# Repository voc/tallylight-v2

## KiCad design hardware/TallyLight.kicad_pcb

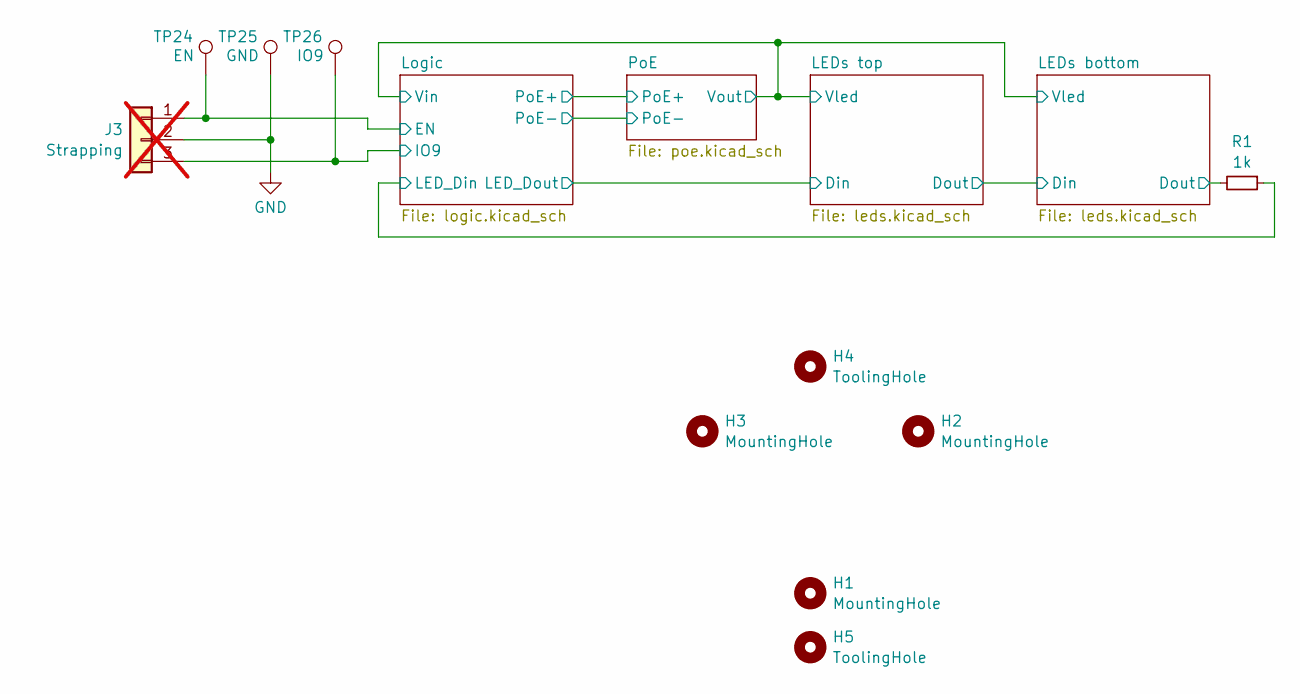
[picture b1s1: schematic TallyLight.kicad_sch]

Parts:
H1, H2, H3: MountingHole; MountingHole_3.2mm_M3
H4, H5: ToolingHole; ToolingHole_JLCSMT
J3: Strapping; PinHeader_1x03_P2.54mm_Vertical; not fitted
R1: 1k; R_0402_1005Metric; LCSC C11702
TP24: EN; TestPoint_Pad_D2.0mm_no_outline
TP25: GND; TestPoint_Pad_D2.0mm
TP26: IO9; TestPoint_Pad_D2.0mm_no_outline

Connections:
/LEDs bottom/Dout: R1.2; also elsewhere on the board
/Logic/EN: J3.1, TP24.1; also elsewhere on the board
/Logic/IO9: J3.3, TP26.1; also elsewhere on the board
/Logic/LED_Din: R1.1; also elsewhere on the board
GND: J3.2, TP25.1; also elsewhere on the board

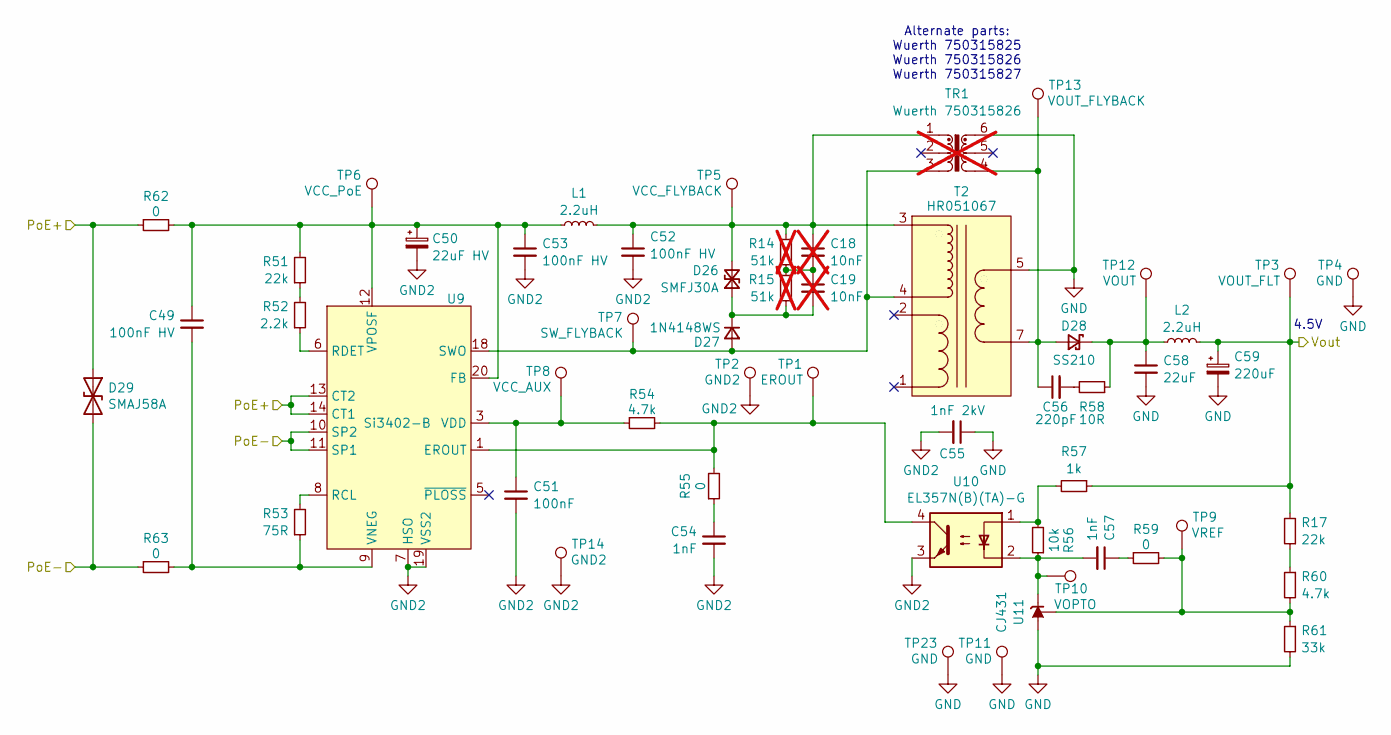
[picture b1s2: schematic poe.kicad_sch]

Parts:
C18, C19: 10nF; C_0402_1005Metric; LCSC C15195; not fitted
C49, C52, C53: 100nF HV; C_0805_2012Metric; LCSC C28233
C50: 22uF HV; CP_Elec_6.3x7.7; LCSC C344075
C51: 100nF; C_0402_1005Metric; LCSC C1525
C54, C57: 1nF; C_0402_1005Metric; LCSC C1523
C55: 1nF 2kV; C_1206_3216Metric; LCSC C9196
C56: 220pF; C_0402_1005Metric; LCSC C1530
C58: 22uF; C_0805_2012Metric; LCSC C45783
C59: 220uF; CP_Elec_6.3x7.7; LCSC C5243829
D26: SMFJ30A; D_SOD-123F; LCSC C151895
D27: 1N4148WS; D_SOD-323; LCSC C2128
D28: SS210; D_SMA; LCSC C14996
D29: SMAJ58A; D_SMA; LCSC C2980408
L1, L2: 2.2uH; L_1008_2520Metric; LCSC C964122
R14, R15: 51k; R_0402_1005Metric; LCSC C25794; not fitted
R17, R51: 22k; R_0402_1005Metric; LCSC C25768
R52: 2.2k; R_0402_1005Metric; LCSC C25879
R53: 75R; R_0603_1608Metric; LCSC C23242
R54, R60: 4.7k; R_0402_1005Metric; LCSC C25900
R55, R59, R62, R63: 0; R_0402_1005Metric; LCSC C17168
R56: 10k; R_0402_1005Metric; LCSC C25744
R57: 1k; R_0402_1005Metric; LCSC C11702
R58: 10R; R_0402_1005Metric; LCSC C25077
R61: 33k; R_0402_1005Metric; LCSC C25779
T2: HR051067; LCSC C93830
TP1: EROUT; TestPoint_Pad_D2.0mm_no_outline
TP2, TP14: GND2; TestPoint_Pad_D2.0mm_trianglular_outline
TP3: VOUT_FLT; TestPoint_Pad_D2.0mm_no_outline
TP4, TP11, TP23: GND; TestPoint_Pad_D2.0mm
TP5: VCC_FLYBACK; TestPoint_Pad_D2.0mm_no_outline
TP6: VCC_PoE; TestPoint_Pad_D2.0mm_no_outline
TP7: SW_FLYBACK; TestPoint_Pad_D2.0mm_no_outline
TP8: VCC_AUX; TestPoint_Pad_D2.0mm_no_outline
TP9: VREF; TestPoint_Pad_D2.0mm_no_outline
TP10: VOPTO; TestPoint_Pad_D2.0mm_no_outline
TP12: VOUT; TestPoint_Pad_D2.0mm_no_outline
TP13: VOUT_FLYBACK; TestPoint_Pad_D2.0mm_no_outline
TR1: Wuerth 750315826; Transformer_Wuerth_750315371; not fitted
U9: Si3402-B; QFN-20-1EP_5x5mm_P0.8mm_EP2.7x2.7mm; LCSC C510771
U10: EL357N(B)(TA)-G; PC817CS_SMD; LCSC C20612591
U11: CJ431; SOT-23; LCSC C3113

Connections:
/LEDs bottom/Vled: C59.1, L2.2, R17.2, R57.1, TP3.1; also elsewhere on the board
/Logic/PoE+: D29.1 (A1), R62.1, U9.13 (CT2), U9.14 (CT1); also elsewhere on the board
/Logic/PoE-: D29.2 (A2), R63.1, U9.10 (SP2), U9.11 (SP1); also elsewhere on the board
GND: C55.1, C58.2, C59.2, R61.2, T2.5, T2.6, TP4.1, TP11.1, TP23.1, TR1.6, U11.3 (A); also elsewhere on the board
GND2: C50.2, C51.2, C52.2, C53.2, C54.2, C55.2, TP2.1, TP14.1, U9.7 (HSO), U9.19 (VSS2), U10.3
unnamed: C18.2, C19.1, R14.1, R15.2
unnamed: C49.2, R53.1, R63.2, U9.9 (VNEG), U9.21 (VNEG)
unnamed: C54.1, R55.1
unnamed: C56.2, R58.2
unnamed: C57.1, R59.1
unnamed: C19.2, D26.1 (A1), D27.1 (K), R15.1
unnamed: C18.1, C52.1, D26.2 (A2), L1.2, R14.2, T2.3, TP5.1, TR1.1
unnamed: D27.2 (A), T2.4, TP7.1, TR1.3, U9.18 (SWO)
unnamed: C56.1, D28.2 (A), T2.7, T2.8, TP13.1, TR1.4
unnamed: C58.1, D28.1 (K), L2.1, R58.1, TP12.1
unnamed: R17.1, R60.1
unnamed: R51.1, R52.2
unnamed: R56.2, R57.2, U10.1
unnamed: R54.2, R55.2, TP1.1, U9.1 (EROUT), U10.4
unnamed: C49.1, C50.1, C53.1, L1.1, R51.2, R62.2, TP6.1, U9.12 (VPOSF), U9.20 (FB)
unnamed: R53.2, U9.8 (RCL)
unnamed: R52.1, U9.6 (RDET)
unnamed: C51.1, R54.1, TP8.1, U9.3 (VDD)
unnamed: C57.2, R56.1, TP10.1, U10.2, U11.2 (K)
unnamed: R59.2, R60.2, R61.1, TP9.1, U11.1 (REF)

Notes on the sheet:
4.5V
Alternate parts: Wuerth 750315825 Wuerth 750315826 Wuerth 750315827

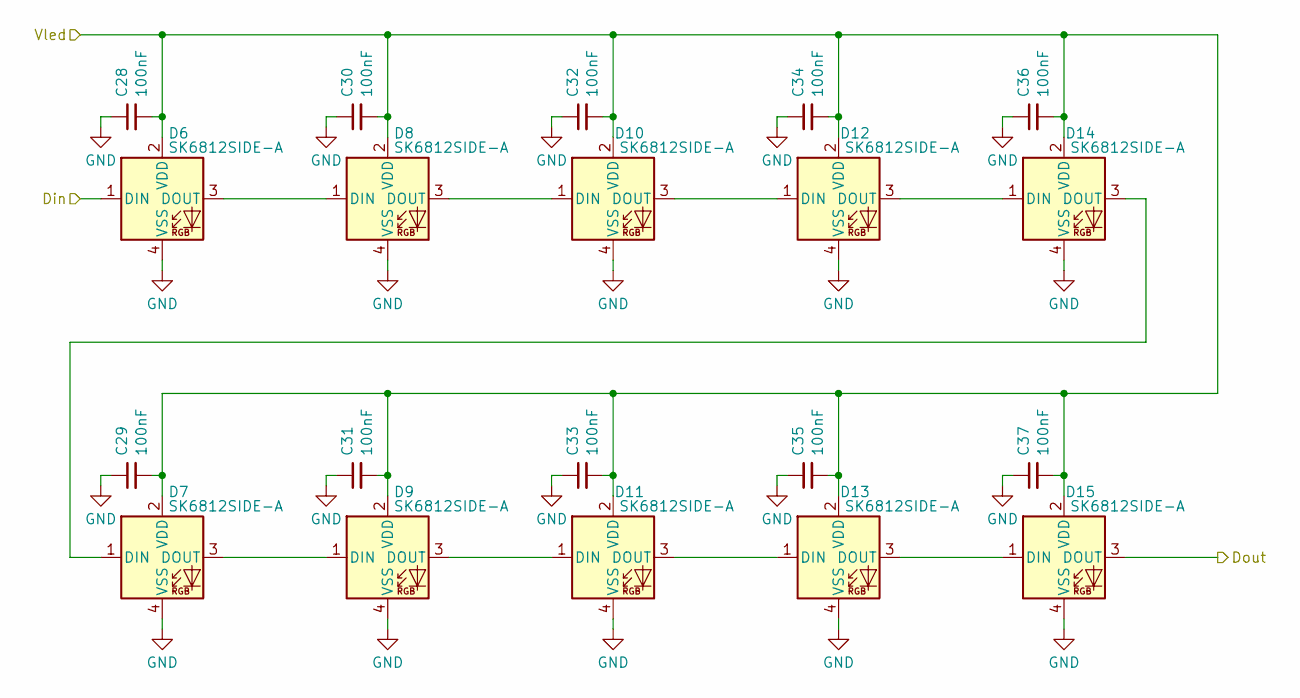
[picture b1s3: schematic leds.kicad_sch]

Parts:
C28, C29, C30, C31, C32, C33, C34, C35, C36, C37: 100nF; C_0402_1005Metric; LCSC C1525
D6, D7, D8, D9, D10, D11, D12, D13, D14, D15: SK6812SIDE-A; LED_SK6812SIDE-A; LCSC C5378721

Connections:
/LEDs bottom/Din: D15.3 (DOUT); also elsewhere on the board
/LEDs bottom/Vled: C28.2, C29.2, C30.2, C31.2, C32.2, C33.2, C34.2, C35.2, C36.2, C37.2, D6.2 (VDD), D7.2 (VDD), D8.2 (VDD), D9.2 (VDD), D10.2 (VDD), D11.2 (VDD), D12.2 (VDD), D13.2 (VDD), D14.2 (VDD), D15.2 (VDD); also elsewhere on the board
/LEDs top/Din: D6.1 (DIN); also elsewhere on the board
GND: C28.1, C29.1, C30.1, C31.1, C32.1, C33.1, C34.1, C35.1, C36.1, C37.1, D6.4 (VSS), D7.4 (VSS), D8.4 (VSS), D9.4 (VSS), D10.4 (VSS), D11.4 (VSS), D12.4 (VSS), D13.4 (VSS), D14.4 (VSS), D15.4 (VSS); also elsewhere on the board
unnamed: D6.3 (DOUT), D8.1 (DIN)
unnamed: D7.3 (DOUT), D9.1 (DIN)
unnamed: D8.3 (DOUT), D10.1 (DIN)
unnamed: D10.3 (DOUT), D12.1 (DIN)
unnamed: D9.3 (DOUT), D11.1 (DIN)
unnamed: D11.3 (DOUT), D13.1 (DIN)
unnamed: D12.3 (DOUT), D14.1 (DIN)
unnamed: D13.3 (DOUT), D15.1 (DIN)
unnamed: D7.1 (DIN), D14.3 (DOUT)

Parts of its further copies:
C38, C39, C40, C41, C42, C43, C44, C45, C46, C47: 100nF; C_0402_1005Metric; LCSC C1525
D16, D17, D18, D19, D20, D21, D22, D23, D24, D25: SK6812SIDE-A; LED_SK6812SIDE-A; LCSC C5378721

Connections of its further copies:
/LEDs bottom/Din: D16.1 (DIN); also elsewhere on the board
/LEDs bottom/Dout: D25.3 (DOUT); also elsewhere on the board
/LEDs bottom/Vled: C38.2, C39.2, C40.2, C41.2, C42.2, C43.2, C44.2, C45.2, C46.2, C47.2, D16.2 (VDD), D17.2 (VDD), D18.2 (VDD), D19.2 (VDD), D20.2 (VDD), D21.2 (VDD), D22.2 (VDD), D23.2 (VDD), D24.2 (VDD), D25.2 (VDD); also elsewhere on the board
GND: C38.1, C39.1, C40.1, C41.1, C42.1, C43.1, C44.1, C45.1, C46.1, C47.1, D16.4 (VSS), D17.4 (VSS), D18.4 (VSS), D19.4 (VSS), D20.4 (VSS), D21.4 (VSS), D22.4 (VSS), D23.4 (VSS), D24.4 (VSS), D25.4 (VSS); also elsewhere on the board
unnamed: D16.3 (DOUT), D18.1 (DIN)
unnamed: D17.1 (DIN), D24.3 (DOUT)
unnamed: D17.3 (DOUT), D19.1 (DIN)
unnamed: D18.3 (DOUT), D20.1 (DIN)
unnamed: D19.3 (DOUT), D21.1 (DIN)
unnamed: D20.3 (DOUT), D22.1 (DIN)
unnamed: D21.3 (DOUT), D23.1 (DIN)
unnamed: D22.3 (DOUT), D24.1 (DIN)
unnamed: D23.3 (DOUT), D25.1 (DIN)

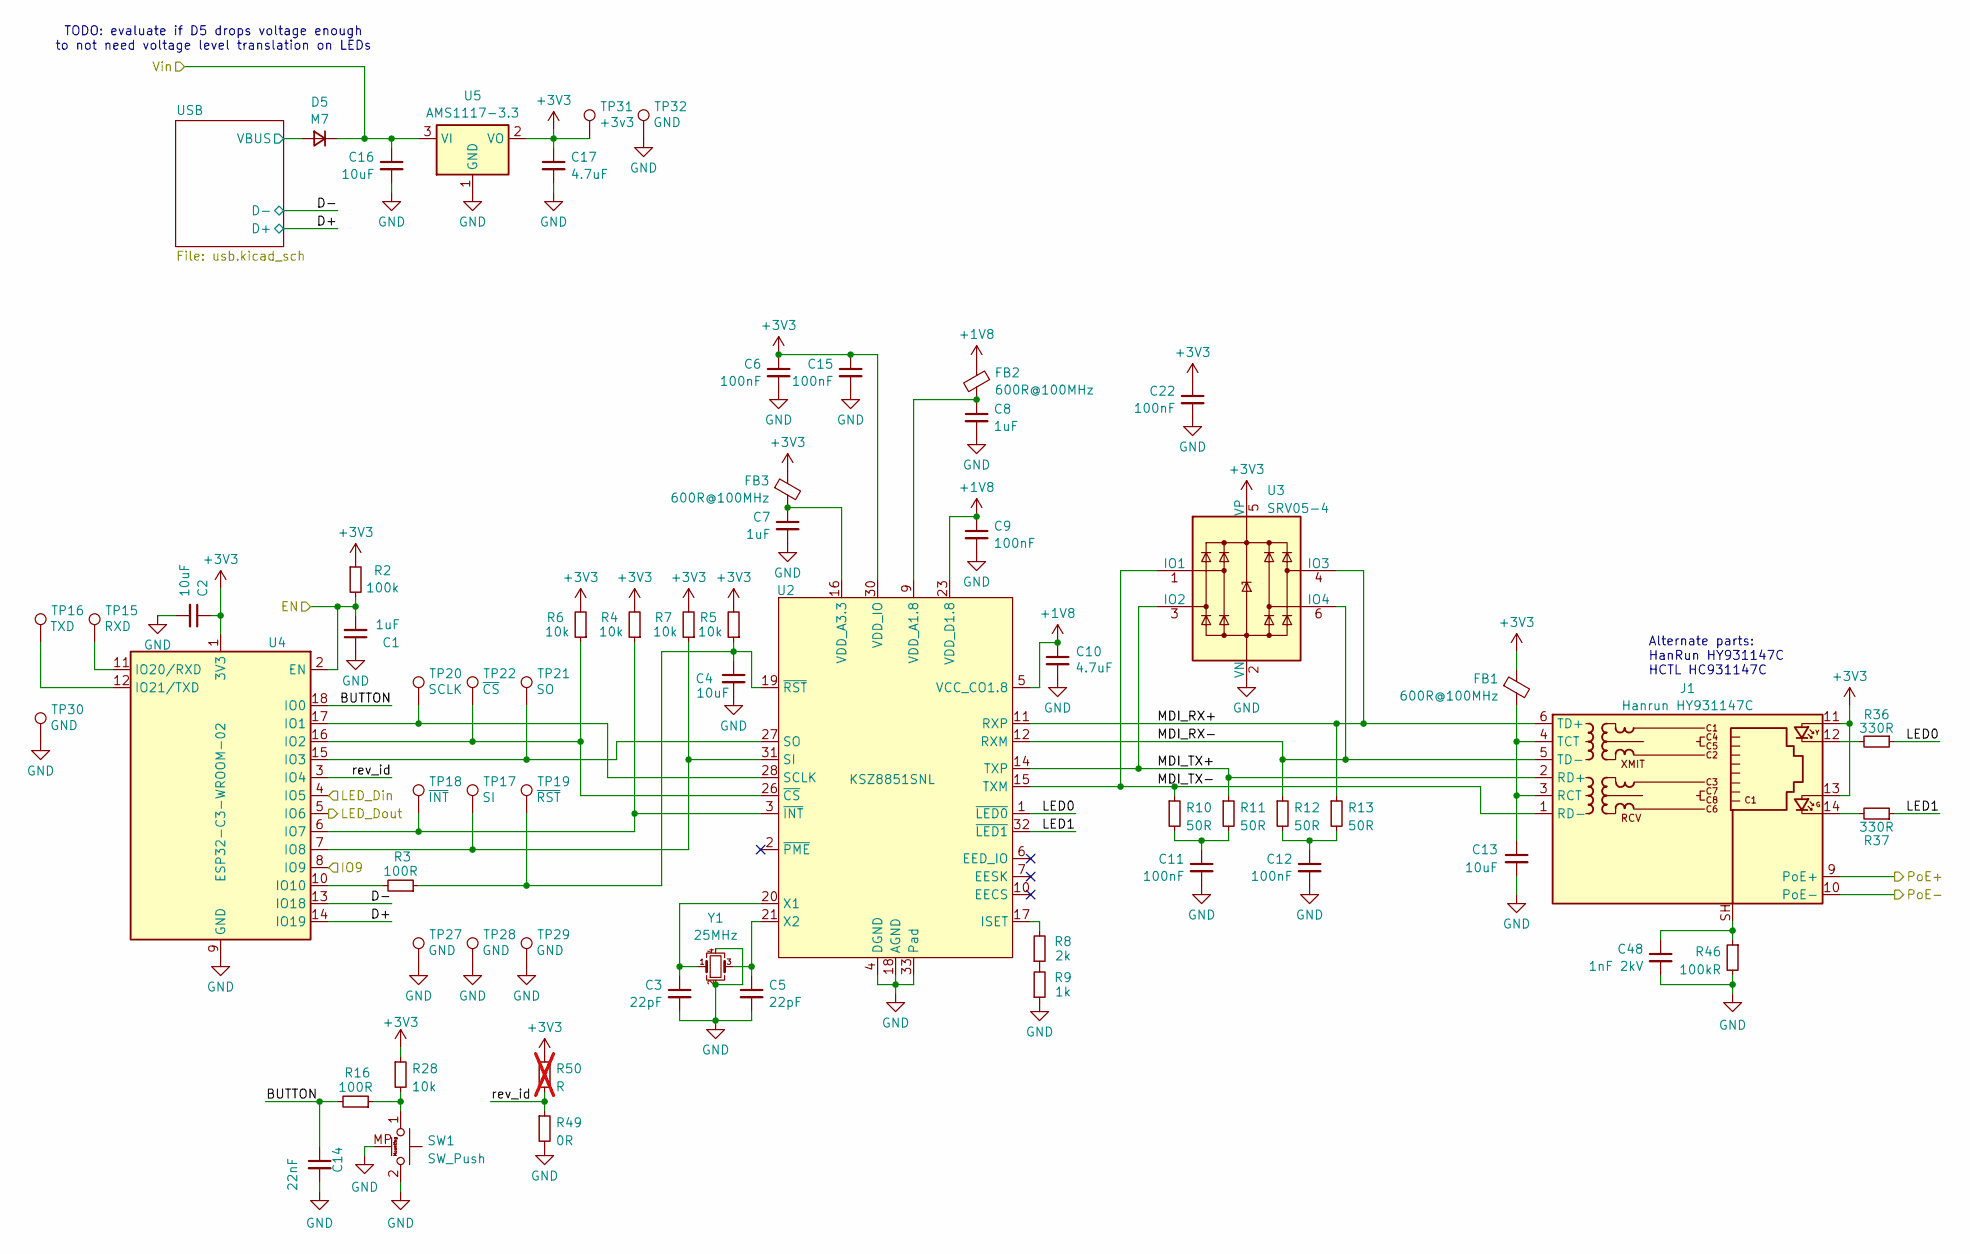
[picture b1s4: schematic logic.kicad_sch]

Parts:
C1, C7, C8: 1uF; C_0402_1005Metric; LCSC C52923
C2, C4, C13: 10uF; C_0402_1005Metric; LCSC C15525
C3, C5: 22pF; C_0402_1005Metric; LCSC C1555
C6, C9, C11, C12, C15, C22: 100nF; C_0402_1005Metric; LCSC C1525
C10, C17: 4.7uF; C_0402_1005Metric; LCSC C23733
C14: 22nF; C_0402_1005Metric; LCSC C1532
C16: 10uF; C_0603_1608Metric; LCSC C96446
C48: 1nF 2kV; C_1206_3216Metric; LCSC C9196
D5: M7; D_SMA; LCSC C95872
FB1, FB2, FB3: 600R@100MHz; L_0402_1005Metric; LCSC C76884
J1: Hanrun HY931147C; RJ45_Hanrun_HY931147C_Horizontal; LCSC C3021372
R2: 100k; R_0402_1005Metric; LCSC C25741
R3, R16: 100R; R_0402_1005Metric; LCSC C25076
R4, R5, R6, R7, R28: 10k; R_0402_1005Metric; LCSC C25744
R8: 2k; R_0402_1005Metric; LCSC C4109
R9: 1k; R_0402_1005Metric; LCSC C11702
R10, R11, R12, R13: 50R; R_0402_1005Metric; LCSC C25120
R36, R37: 330R; R_0402_1005Metric; LCSC C25104
R46: 100kR; R_1206_3216Metric; LCSC C17900
R49: 0R; R_0402_1005Metric; LCSC C17168
R50: R; R_0402_1005Metric; not fitted
SW1: SW_Push; KEY-TH_4P-L7.5-W6.8-P4.50-LS7.2; LCSC C266183
TP15: RXD; TestPoint_Pad_D2.0mm_no_outline
TP16: TXD; TestPoint_Pad_D2.0mm_no_outline
TP17: SI; TestPoint_Pad_D2.0mm_no_outline
TP18: ~{INT}; TestPoint_Pad_D2.0mm_no_outline
TP19: ~{RST}; TestPoint_Pad_D2.0mm_no_outline
TP20: SCLK; TestPoint_Pad_D2.0mm_no_outline
TP21: SO; TestPoint_Pad_D2.0mm_no_outline
TP22: ~{CS}; TestPoint_Pad_D2.0mm_no_outline
TP27, TP28, TP29, TP30, TP32: GND; TestPoint_Pad_D2.0mm
TP31: +3v3; TestPoint_Pad_D2.0mm_no_outline
U2: KSZ8851SNL; QFN-32-1EP_5x5mm_P0.5mm_EP3.1x3.1mm_ThermalVias; LCSC C633272
U3: SRV05-4; SOT-23-6; LCSC C85364
U4: ESP32-C3-WROOM-02; LCSC C2934560
U5: AMS1117-3.3; SOT-223-3_TabPin2; LCSC C6186
Y1: 25MHz; Crystal_SMD_3225-4Pin_3.2x2.5mm; LCSC C9006

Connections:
+1V8: C9.1, C10.1, FB2.1, U2.5 (VCC_CO1.8), U2.23 (VDD_D1.8)
+3V3: C2.1, C6.1, C15.1, C17.1, C22.1, FB1.1, FB3.1, J1.11, J1.13, R2.1, R4.2, R5.2, R6.2, R7.2, R28.1, R50.1, TP31.1, U2.25 (VDD_IO), U2.30 (VDD_IO), U3.5 (VP), U4.1 (3V3), U5.2 (VO); also elsewhere on the board
/LEDs bottom/Vled: C16.1, D5.1 (K), U5.3 (VI); also elsewhere on the board
/LEDs top/Din: U4.5 (IO6); also elsewhere on the board
/Logic/BUTTON: C14.1, R16.2, U4.18 (IO0)
/Logic/D+: U4.14 (IO19); also elsewhere on the board
/Logic/D-: U4.13 (IO18); also elsewhere on the board
/Logic/EN: C1.2, R2.2, U4.2 (EN); also elsewhere on the board
/Logic/IO9: U4.8 (IO9); also elsewhere on the board
/Logic/LED0: R36.1, U2.1 (~LED0)
/Logic/LED1: R37.1, U2.32 (~LED1)
/Logic/LED_Din: U4.4 (IO5); also elsewhere on the board
/Logic/MDI_RX+: J1.6 (TD+), R13.1, U2.11 (RXP), U3.4 (IO3)
/Logic/MDI_RX-: J1.5 (TD-), R12.1, U2.12 (RXM), U3.6 (IO4)
/Logic/MDI_TX+: J1.2 (RD+), R11.1, U2.14 (TXP), U3.3 (IO2)
/Logic/MDI_TX-: J1.1 (RD-), R10.1, U2.15 (TXM), U3.1 (IO1)
/Logic/PoE+: J1.9 (PoE+); also elsewhere on the board
/Logic/PoE-: J1.10 (PoE-); also elsewhere on the board
/Logic/USB/VBUS: D5.2 (A); also elsewhere on the board
/Logic/rev_id: R49.1, R50.2, U4.3 (IO4)
GND: C1.1, C2.2, C3.2, C4.2, C5.2, C6.2, C7.2, C8.2, C9.2, C10.2, C11.2, C12.2, C13.2, C14.2, C15.2, C16.2, C17.2, C22.2, C48.2, R9.1, R46.2, R49.2, SW1.2, SW1.MP, TP27.1, TP28.1, TP29.1, TP30.1, TP32.1, U2.4 (DGND), U2.8 (AGND), U2.13 (AGND), U2.18 (AGND), U2.22 (DGND), U2.24 (DGND), U2.29 (DGND), U2.33 (Pad), U3.2 (VN), U4.9 (GND), U4.19 (GND), U5.1 (GND), Y1.2, Y1.4; also elsewhere on the board
unnamed: C11.1, R10.2, R11.2
unnamed: C12.1, R12.2, R13.2
unnamed: C48.1, J1.SH, R46.1
unnamed: J1.12, R36.2
unnamed: J1.14, R37.2
unnamed: C13.1, FB1.2, J1.3 (RCT), J1.4 (TCT)
unnamed: R8.1, R9.2
unnamed: R16.1, R28.2, SW1.1
unnamed: R8.2, U2.17 (ISET)
unnamed: TP20.1, U2.28 (SCLK), U4.17 (IO1)
unnamed: R7.1, TP17.1, U2.31 (SI), U4.7 (IO8)
unnamed: TP21.1, U2.27 (SO), U4.15 (IO3)
unnamed: C8.1, FB2.2, U2.9 (VDD_A1.8)
unnamed: C7.1, FB3.2, U2.16 (VDD_A3.3)
unnamed: C3.1, U2.20 (X1), Y1.1
unnamed: C5.1, U2.21 (X2), Y1.3
unnamed: R6.1, TP22.1, U2.26 (~CS), U4.16 (IO2)
unnamed: R4.1, TP18.1, U2.3 (~INT), U4.6 (IO7)
unnamed: C4.1, R3.1, R5.1, TP19.1, U2.19 (~RST)
unnamed: R3.2, U4.10 (IO10)
unnamed: TP15.1, U4.11 (IO20/RXD)
unnamed: TP16.1, U4.12 (IO21/TXD)

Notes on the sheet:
Alternate parts: HanRun HY931147C HCTL HC931147C
TODO: evaluate if D5 drops voltage enough to not need voltage level translation on LEDs

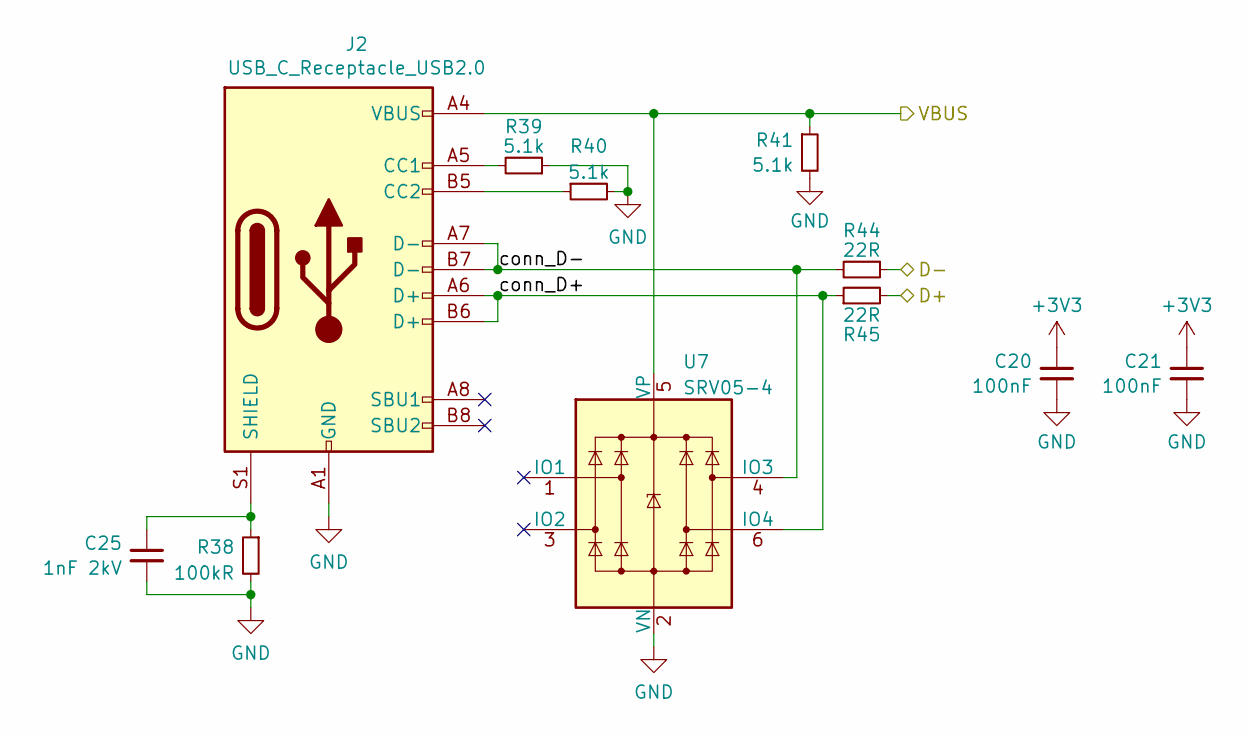
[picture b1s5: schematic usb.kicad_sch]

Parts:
C20, C21: 100nF; C_0402_1005Metric; LCSC C1525
C25: 1nF 2kV; C_1206_3216Metric; LCSC C9196
J2: USB_C_Receptacle_USB2.0; USB_C_Receptacle_Palconn_UTC16-G; LCSC C167321
R38: 100kR; R_1206_3216Metric; LCSC C17900
R39, R40, R41: 5.1k; R_0402_1005Metric; LCSC C25905
R44, R45: 22R; R_0402_1005Metric; LCSC C25092
U7: SRV05-4; SOT-23-6; LCSC C85364

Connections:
+3V3: C20.1, C21.1; also elsewhere on the board
/Logic/D+: R45.2; also elsewhere on the board
/Logic/D-: R44.1; also elsewhere on the board
/Logic/USB/VBUS: J2.A4 (VBUS), J2.A9 (VBUS), J2.B4 (VBUS), J2.B9 (VBUS), R41.1, U7.5 (VP); also elsewhere on the board
/Logic/USB/conn_D+: J2.A6 (D+), J2.B6 (D+), R45.1, U7.6 (IO4)
/Logic/USB/conn_D-: J2.A7 (D-), J2.B7 (D-), R44.2, U7.4 (IO3)
GND: C20.2, C21.2, C25.2, J2.A1 (GND), J2.A12 (GND), J2.B1 (GND), J2.B12 (GND), R38.2, R39.1, R40.2, R41.2, U7.2 (VN); also elsewhere on the board
unnamed: J2.A5 (CC1), R39.2
unnamed: J2.B5 (CC2), R40.1
unnamed: C25.1, J2.S1 (SHIELD), R38.1

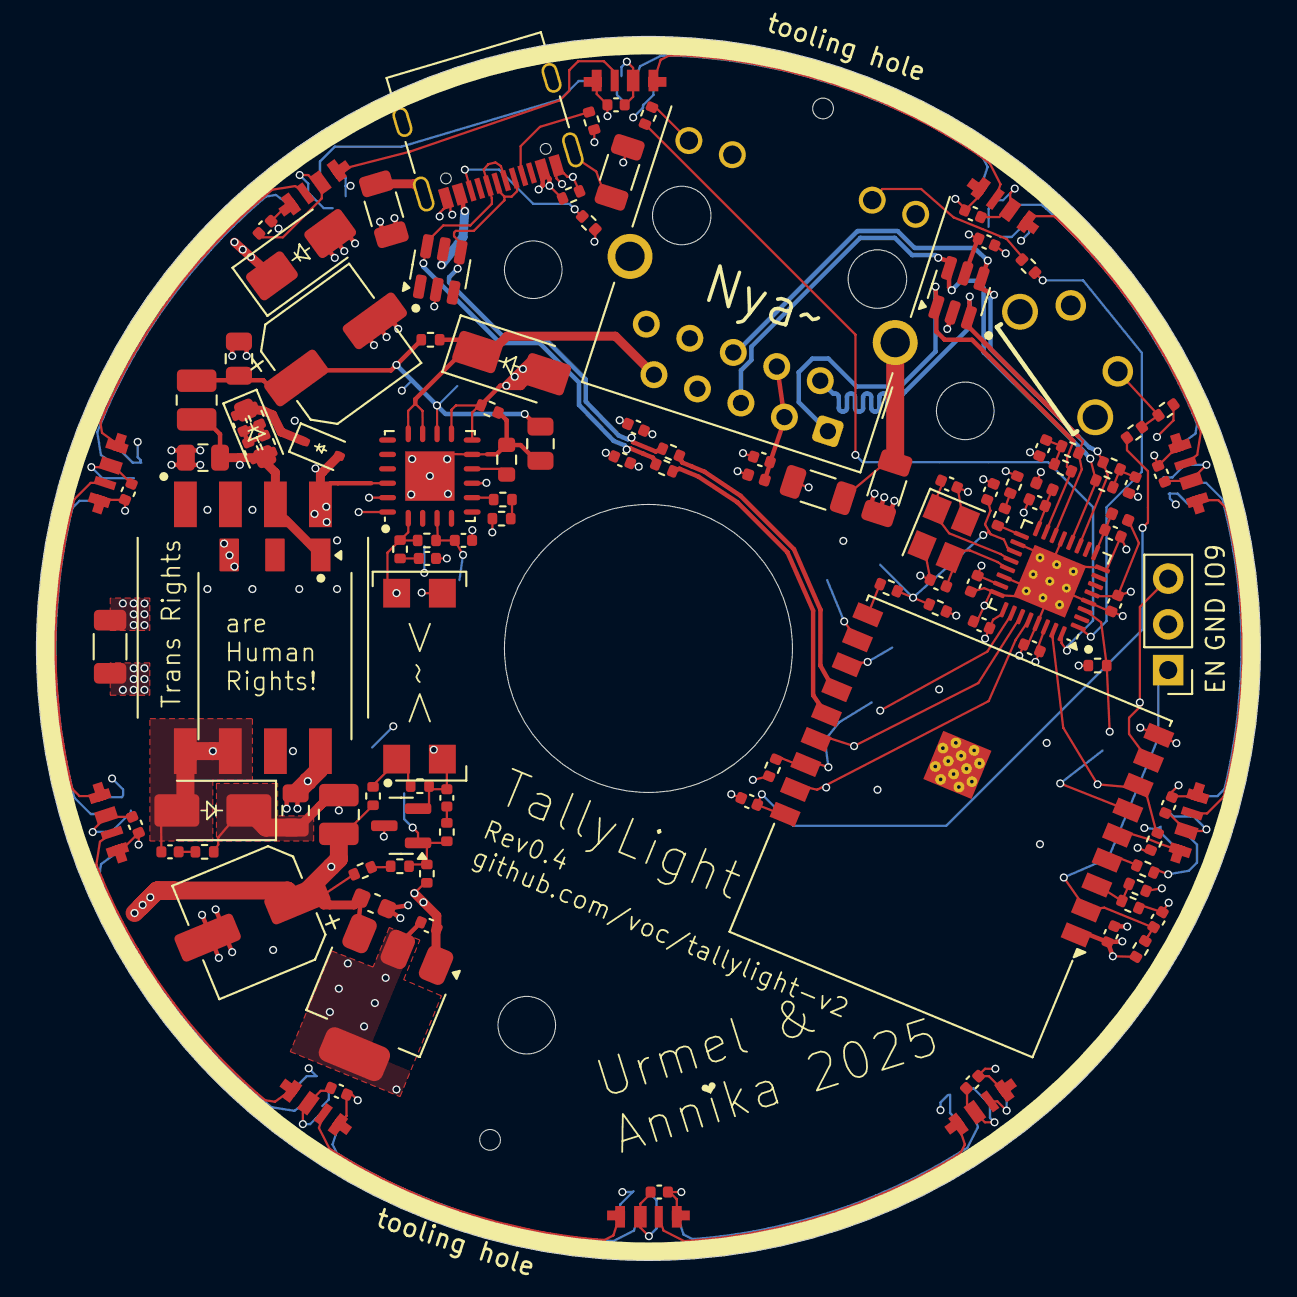
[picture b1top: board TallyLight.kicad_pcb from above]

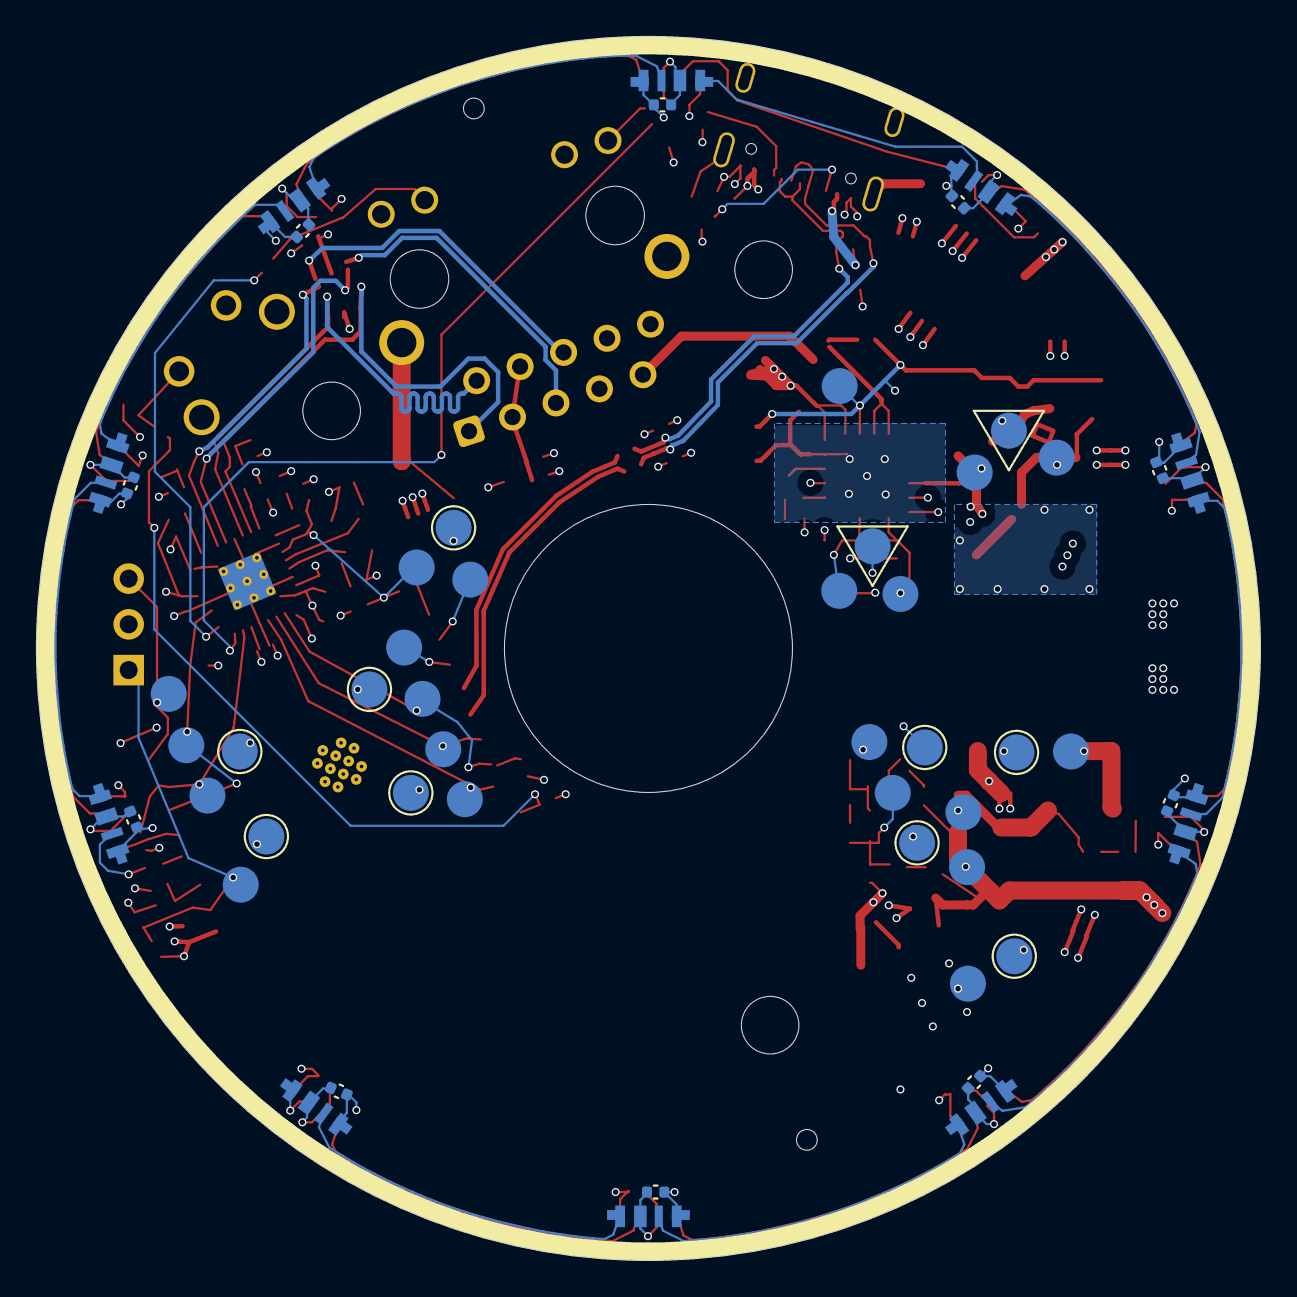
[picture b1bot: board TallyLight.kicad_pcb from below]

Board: 4 copper layers, 68.0 x 68.0 mm, 179 parts (52 on the bottom side), 89 nets.

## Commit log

2025-02-13 Add initial rev0 schematic and layout
    First rough draft
2025-02-13 Add OpenSCAD crime^w°winitial case design
2025-03-02 hardware: case: add transparent ring to improve light transmission
2025-03-02 hardware: switch to ESP32-C3 MCU and Si3402-B for PoE
    Further changes:
    - Enlarge center hole to 16mm diameter
    - Replace Ethernet Phy by KSZ8851 SPI MAC + Phy
2025-03-02 hardware: add missing pin 1 indicator to optocoupler U10
2025-03-02 hardware: replace ESP32-C3 MINI by more common WROOM-02 module
2025-03-02 hardware: add testpoints to flyback converter and SPI MAC + Phy
    Add testpoints to all critical section that might require in-circuit
    debugging
2025-03-02 hardware: add small thermal plane to PoE controller
2025-03-02 hardware: pull up GPIO2
    There is a bit of an ominous sentence in the ESP32-C3 datasheet:
    "GPIO2 actually does not determine SPI Boot and Joint Download Boot mode,
    but it is recommended to pull this pin up due to glitches."
    Switch GPIO2 to an input pin on the KSZ8851 and pull it up to VDD to avoid
    any possible issues.
2025-03-02 hardware: add alternate snubber and flyback footprints
2025-03-02 hardware: add LCSC partnumber to ESP32-C3 module
2025-03-02 hardware: upgrade decoupling caps on ferrite beads to 1µF
2025-03-19 Implement review comments by Urmel
2025-03-20 Make button trace around center hole more round
2025-03-22 Exclude parts with virtual footprints from BOM
2025-03-22 Exclude bottom side LEDs and associated passives from position file
2025-03-22 Add full size quater inch insert support column
2025-04-11 Optimize flyback feedback loop stability
    During load testing on an initial prototype better component values for the
    flyback feedback loop were found. Update design with those.
2025-04-21 Improve heatsinking on secondary side flyback rectifier diode
    The diode can get a bit hot under high load.
    Improve its cooling.
2025-05-12 wip rust fw
2025-05-12 cargo fmt
2025-05-20 tx/rx kinda working
2025-05-20 missing file
2025-05-26 wip rpc and stuff
2025-05-27 bump deps
2025-06-06 tallytool wip
2025-06-06 rpc wip config
2025-06-06 Use patches, split owned/borrowed msg defs
2025-06-06 Remove thing I was just testing
2025-11-07 rev 0.4 move button next to ethernet jack, kicad v9
2025-12-31 Update button footprint library reference
    The library symbol was previously changed in the PCB design file only.
    Relfect that change in the schematic, too.
2025-12-31 Remove stubs from Ethernet TVS
2025-12-31 Update button footprint library reference
    The library symbol was previously changed in the PCB design file only.
    Reflect that change in the schematic, too.
2026-01-03 update button lcsc part to shorter variant
